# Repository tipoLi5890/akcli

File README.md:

<div align="center">

<p><strong>The verification layer that makes AI-written KiCad schematics safe to apply — a zero-dependency (pure-stdlib Python) CLI.</strong></p>

<p>

</p>

<p><strong>English</strong> · <a href=".github/README.zh-Hant.md">繁體中文</a> · <a href=".github/README.zh-Hans.md">简体中文</a> · <a href=".github/README.ja.md">日本語</a></p>

</div>

---

**akcli** is a zero-dependency Python CLI for **AI-native schematic design on KiCad** — a scriptable
design loop that you or **any AI agent** can drive end to end (bundled plugins/skills ship for Claude
Code, Codex, and OpenCode, but a shell is all it takes). Writing is the capability; verification is what makes it safe to use —
every edit is dry-run by default, net-diffed and connectivity-gated. Author a `.kicad_sch` from a JSON op-list,
run ERC / design-review / BOM / schematic ↔ PCB checks, simulate on ngspice, and source real
JLCPCB/LCSC parts. Existing Altium `.SchDoc` / `.SchLib` / `.PcbDoc` / `.PcbLib` designs import
read-only — an on-ramp into the KiCad flow, which is where all development happens.

## Install

Zero runtime dependencies; needs **Python ≥ 3.11** (for stdlib `tomllib`). The distribution is
`akcli-kicad`; the command is `akcli`:

```bash
pipx install akcli-kicad        # or: pip install akcli-kicad
akcli --version

# or run straight from a clone, no install
git clone https://github.com/tipoLi5890/akcli
./akcli/bin/akcli --help        # wrapper auto-selects a Python ≥ 3.11
```

Claude Code plugin (marketplace name `akcli`):

```text
/plugin marketplace add tipoLi5890/akcli
/plugin install akcli@akcli
```

Codex plugin (same name `akcli`):

```bash
codex plugin marketplace add tipoLi5890/akcli   # or `add ./` from a clone
codex plugin install akcli@akcli
```

Full details, per-agent setup, and troubleshooting in [INSTALL.md](INSTALL.md).

## Quickstart

Scaffold a real KiCad project with a worked example, then read, check, and draw into it — straight
from the shell:

```bash
akcli project new demo --example voltage-divider                  # .kicad_pro/.kicad_sch/.kicad_pcb/lib tables/ops.json
cd demo
akcli read  demo.kicad_sch --summary                              # normalized JSON, context-budgeted
akcli check demo.kicad_sch                                        # ERC-lite + power + BOM + connectivity + integrity
akcli draw  demo.kicad_sch --ops ops.json                         # dry-run: shows changes + net diff
akcli draw  demo.kicad_sch --ops ops.json --apply --strict-nets   # atomic write + verify + backup
akcli project check                                               # project-integrity findings (still 0)
akcli undo  demo.kicad_sch                                        # revert the last write
```

Every write is a dry run by default; `--apply` goes through an atomic snapshot → temp → verify →
replace pipeline with a pure-Python connectivity gate, and `akcli undo` reverts from a rotated backup
stack. Altium files are read-only offline.

## What it does

One normalized model behind every command, so each check, diff, and report works on a KiCad
`.kicad_sch` — and just the same on an imported Altium `.SchDoc`:

| Command | What it does |
|---|---|
| `read` · `net` · `component` · `pins` | Parse KiCad or Altium into one normalized JSON model; query nets (whole-net or pin-level: `net --at` / `--same` / `--why`), components, and pin coordinates. |
| `project` · `new` · `plan` · `draw` · `ops` · `arrange` | Scaffold a complete KiCad project (`.kicad_pro`/`.kicad_pcb`/lib tables, optionally `--example NAME`) from scratch, or adopt an existing `.kicad_sch` into one (`project new`/`project init`), inspect what it binds (`project info`) and gate its integrity (`project check`), then author it — a root file, a child sheet, or **several sheets in one atomic transaction** (the `sheets` envelope + per-op `sheet` routing, with run backups and `undo --run`) — from a versioned **22-op + 10-macro** JSON op-list, behind a net-diff safety gate evaluated over the **whole sheet tree** and one-command `undo`; `ops from-intent` compiles a design document (declared nets + components) straight into an op-list. Symbols resolve from `--symbols`, the config paths, then the project and global `sym-lib-table`. |
| `check` · `verify` · `diff` · `pinmap` | ERC-lite + power + BOM + document-integrity + intent / contract checks, schematic ↔ PCB equivalence (`verify --library` also compares each board footprint with its library source), net-membership diff, MCU pin → net map. |
| `review` | Advisory, confidence-graded design review across six detector families (signal / validation / pcb / emc / domain / gerber); DNP parts satisfy no rule. |
| `sim` | Render to a SPICE deck and assert on KiCad's bundled ngspice; sweep corners; fit diode models from datasheet points. Component values are normalized, or refused rather than guessed. |
| `jlc` | Search JLCPCB/LCSC (stock, price, Basic/Extended), convert a part into a KiCad library in-process (typed pins, real `Value`), fetch datasheets. |
| `calc` | **60** standards-cited offline calculators (E-series, IPC-2221, impedance, I²C pull-ups, buck/boost…), each citing its reference. |
| `library` · `fab` · `release` | Library-workspace audit/repair, symbol authoring from a pin table (`new-symbol` — you give the pin table, akcli computes the coordinates) with a standalone lint (`lint-symbols`) and a coincident-pin check that gates the write, versioned fab-profile checks (bundled profiles selectable by id via `fab profiles`; the real outline, vias, tenting and project design rules are read from the board), a committed library baseline (`library audit --write-baseline`), and a release preflight (including KiCad DRC) that writes a traceable manifest with tool, gerber and profile evidence. |
| `gate` | Iteration-weight bundle of the four checks re-run after every GUI edit round (the full `check` set, intent assertions, sch ↔ PCB `verify`, BOM-lock drift — offline by default) — zero-argument in a configured project; `release preflight` stays the release-weight gate. |
| `export` · `render` · `doc` · `view` | Netlist export (Protel / KiCad / CSV — the KiCad form carries the UUID sheetpath identity a re-import needs), pure-stdlib SVG render, a Markdown pinout book, and a localhost `/calc` + `/live` dashboard. |
| `capabilities` · `schema` | The self-describing surface manifest — whole, per-section (`--section`), or per-command (`--command draw`) — and every packaged JSON Schema printed byte-for-byte for client-side validation. |

Two headline examples — a design review and a part search:

```bash
akcli review analyze board.kicad_sch --profile deep --pcb board.kicad_pcb   # advisory findings + evidence
akcli jlc search "0.1uF 0402 X7R"                                           # JLCPCB/LCSC catalog (needs network)
```

## Use with AI agents

`akcli` is a plain CLI, so any shell-capable agent can drive it. Commands emit structured JSON with
`--json` (carrying a version stamp — `schema_version`, or a family field like `proposals_version` /
`facts_version`), each op-list carries a `protocol_version`, and `akcli
capabilities` self-describes the entire CLI surface in one JSON document — and every error code ships a
machine-readable `remediation` hint.

- **Claude Code** — install the bundled plugin for 8 `/akcli:circuit-*` commands (review, pinmap,
  draw, diff, parts, sim, datasheet, release) plus 13 skills spanning design, review, authoring, Altium interop, parts
  sourcing, calculators, and release gating.
- **Codex** — install the bundled plugin, or drop the loose skill folders into `.agents/skills/` for
  auto-discovery. See [docs/codex-plugin.md](docs/codex-plugin.md).
- **OpenCode** — auto-discovers the bundled skills; see
  [INSTALL.md](INSTALL.md#use-with-ai-coding-agents) for the exact commands.

## Why akcli

- **Zero runtime dependencies.** Standard library only (including `tomllib`) — easy to vendor, sandbox,
  or run in CI.
- **Purpose-built for KiCad.** An iterative KiCad S-expression parser and byte-stable writer at the
  core; Altium designs come in read-only through pure-stdlib OLE2/CFBF record decoding, straight into
  the same KiCad flow. No compiled extensions.
- **Byte-identical re-apply.** Deterministic UUIDv5 + replace-in-place makes every edit idempotent —
  re-running an op-list produces the same bytes.
- **Connectivity is the only hard write gate.** Every `plan`/`draw` prints a before/after net diff
  (splits, merges, moves, renames — matched by pin membership, never by name); `--strict-nets` refuses a
  write that splits, merges or moves a named net.
- **Net inference you can trust.** A rebuilt net layer handles global same-name merges, junctions,
  T-junctions, and No-ERC markers — fixing the classic "same-named nets split into single-pin nets" bug.

## Optional external tools

"Zero-dependency" means zero Python **package** dependencies: `pip install` pulls in nothing, and the
entire core loop (read / plan / draw / check / diff / calc / render) runs on the standard library
alone. A few features can use something outside Python — always detected at runtime, never required
by the core loop:

| Feature | Uses | If missing |
|---|---|---|
| Advisory ERC second opinion, `view live` SVG | `kicad-cli` (local executable) | Skipped silently — non-fatal, results stay advisory. |
| `sim` execution (`--deck-only` needs nothing) | libngspice (bundled with KiCad) | `sim` exits with `NGSPICE_MISSING`; everything else unaffected. |
| Standard symbol nicknames (`Device:R`, `power:*`) | `kicad-cli` install location (derives `${KICAD*_SYMBOL_DIR}`) | Symbols resolve only from explicit `--symbols` / config paths. |
| `jlc` part search / datasheet fetch | Network | The **only** networked command family; all others are fully offline. |

`akcli doctor` probes each of these and prints per-OS remediation.

## Documentation

| Doc | Covers |
|---|---|
| [SPEC.md](docs/SPEC.md) | Data model, config tables, JSON schemas |
| [cli-reference.md](docs/cli-reference.md) | Every command and flag |
| [op-list-authoring.md](docs/op-list-authoring.md) | Op-list authoring bible (ops, macros, groups) |
| [design-integrity.md](docs/design-integrity.md) | Contracts, fab profiles, release preflight |
| [review-rules.md](docs/review-rules.md) | Design-review rule catalogue |
| [sim.md](docs/sim.md) | Simulation reference |
| [agent-state.md](docs/agent-state.md) | Workspace state files and the multi-agent contract |
| [codex-plugin.md](docs/codex-plugin.md) | Codex plugin layout and bundled skills |
| [jlc.md](docs/jlc.md) | `akcli jlc`: part search, BOM purchasability, datasheet fetch, JLCPCB manufacturing handoff |
| [kicad-format-gotchas.md](docs/kicad-format-gotchas.md) | KiCad file-format rules for safe editing |
| [pin-identity.md](docs/pin-identity.md) | Pin identity model audit ahead of v1.0 |
| [migration-0.21.md](docs/migration-0.21.md) | Migrating to the 0.21 contract (`protocol_version` 2, schema 2.0) |
| [releasing.md](docs/releasing.md) | Release runbook |
| [recipes/](docs/recipes/README.md) | CI workflow recipes (gating schematic pull requests) |
| [stability.md](docs/stability.md) | Public contract surfaces, what is not contract, versioning rules |
| [ROADMAP.md](ROADMAP.md) | Roadmap to v1.0 with exit criteria |

## Roadmap

**Shipped (v0.24.0):** release gates for KiCad DRC, a committed library baseline, a PCB ↔ library
check and tree-scoped integrity, with `fab check` reading the board's real outline, vias, tenting and
project design rules; before that, complete KiCad project scaffolding — `project new` / `project init` write the
`.kicad_pro`, a blank `.kicad_pcb` board container, the project lib tables and a `.gitignore` around a
root sheet (`--example NAME` drops in a worked op-list), while `project info` / `project check` read
and gate what the project binds — KiCad write/draw from a 22-op + 10-macro vocabulary (hierarchical
`add_sheet`, optionally creating the child sheet inside the same transaction with `"create": true`,
writes into a child sheet of an existing hierarchy and across several sheets in one atomic
transaction, a net-diff safety rail evaluated over the whole sheet tree, per-instance references on
a reused sheet, `new` / multi-level `undo` / `undo --run`), net-preserving `arrange --groups` re-layout, the advisory `akcli review` engine (six
detector families, now including power-entry protection, plus a datasheet facts store, `propose` /
`tree` / `validate`), ERC / power / BOM / diff / pinmap / intent / contract checks with waivers
(SARIF from `check --format sarif` / `review report --format sarif`), read-only document `check --integrity`, schematic ↔ PCB `verify`, a project `library`
workspace, versioned `fab` profiles, a `release preflight` gate, `akcli sim` on KiCad's bundled
ngspice, JLCPCB/LCSC sourcing with datasheet fetch, 60 standards-cited calculators, pure-stdlib SVG
rendering that draws the real symbol artwork from KiCad `lib_symbols`, and version-tolerant
Altium/KiCad readers. Standard symbol nicknames resolve on a stock KiCad install: the compiled-in
`${KICAD*_SYMBOL_DIR}` paths are derived from the located `kicad-cli`, and `akcli doctor` reports
whether that resolution works here.

**Ahead (→ v1.0):** the contract-freeze audit. The first PyPI release (`pip install akcli-kicad`) shipped in 0.15.0.
A workflow recipe that gates schematic PRs ships in [docs/recipes/](docs/recipes/README.md). *Deferred
by decision:* a packaged Marketplace Action, the `view` waveform panel, and a native MCP server (the
plain CLI serves agents today). Full plan with exit criteria in
[ROADMAP.md](ROADMAP.md).

## Acknowledgments

`akcli jlc` builds on (full attribution in [ACKNOWLEDGMENTS.md](ACKNOWLEDGMENTS.md) and
[THIRD_PARTY_NOTICES.md](THIRD_PARTY_NOTICES.md)):

- **JLC2KiCadLib** by **TousstNicolas** (MIT) — LCSC → KiCad conversion core, vendored.
- **jlcsearch** (tscircuit, MIT) and **jlcparts** (MIT) — part-search backend.
- **EasyEDA / LCSC / JLCPCB** — component data source.

## Contact

Questions, bugs, or feature requests: please
[open a GitHub issue](https://github.com/tipoLi5890/akcli/issues).

## License

MIT © 2026 Li, ching yu. See [LICENSE](LICENSE); third-party attribution in
[ACKNOWLEDGMENTS.md](ACKNOWLEDGMENTS.md) and [THIRD_PARTY_NOTICES.md](THIRD_PARTY_NOTICES.md), and the
security model in [SECURITY.md](SECURITY.md).

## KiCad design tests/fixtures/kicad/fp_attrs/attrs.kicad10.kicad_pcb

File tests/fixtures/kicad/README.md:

# Synthetic KiCad fixtures

Hand-authored, valid S-expression KiCad files used by the KiCad reader/netbuild tests.
The dev/CI box has **no KiCad libraries installed**, so every symbol these schematics
reference is vendored here and also cached inline (`lib_symbols`) in each schematic.
Every **schematic** here is hand-authored — coordinates and UUIDs are hand-chosen so the
files are small and reviewable. The exceptions are the three `netlist_*.kicad10.net` files,
which *are* real `kicad-cli` exports kept as netlist ground truth (see below).

## Netlist ground truth

`netlist_power_entry.kicad10.net` — `kicad-cli 10.0.4 sch export netlist` run on
`tests/fixtures/corpus/power_entry.kicad_sch`. It pins the grammar and the UUID identity
(`(design)`, per-comp `(sheetpath)` + `(tstamps)`, `(libparts)`) that
`src/akcli/exporters.py` must agree with, so `tests/test_e2e_netlist.py` can arbitrate the
exporter **everywhere**, not only on a box with KiCad installed (where the same test
re-derives it live and asserts the fixture has not rotted).

`netlist_hier_root.kicad10.net` — the same, run on `hier/root.kicad_sch` (below). It pins
**net NAMING** across a hierarchy, the rule a flat board cannot show.

Four machine-specific atoms were normalized on commit; nothing structural was touched:

| Field | KiCad wrote | Committed as |
|---|---|---|
| `(design (source ..))` | absolute path of the dev checkout | repo-relative posix path |
| `(design (date ..))` | export wall-clock time | `""` (determinism) |
| `(comp (property (name "Sheetname") (value ..)))` | localized root-sheet name | `"Root"` |
| `(libraries (library (uri ..)))` | `${KICAD10_SYMBOL_DIR}` | `${KICAD_SYMBOL_DIR}` |

## `hier/` — hierarchical net-name ground truth

`hier/root.kicad_sch` instantiates `hier/amp.kicad_sch` **twice** (`Amp`, `Amp Two`), and
that child instantiates `hier/deep.kicad_sch` once (`Deep`) — five sheet instances in all.
It exists to pin one rule: eeschema qualifies a net name with the **human-readable sheet
path** of its driver, unless the driver is a global label or a power pin.

| driver | net name KiCad writes |
|---|---|
| `(label "ROOT_LOCAL")` on the root sheet | `/ROOT_LOCAL` |
| `(label "AMP_LOCAL")` on a child sheet | `/Amp/AMP_LOCAL`, `/Amp Two/AMP_LOCAL` |
| `(label "DEEP_LOCAL")` on a grandchild sheet | `/Amp/Deep/DEEP_LOCAL` |
| `(hierarchical_label "DEEP_OUT")`, parent pin unlabelled | `/Amp/Deep/DEEP_OUT` |
| `(global_label "AMP_GLOBAL")` | `AMP_GLOBAL` — never qualified |
| `power:GND` symbol | `GND` — never qualified |

Every net here carries exactly **one** name, so the fixture tests the qualification rule
without depending on how ties between several names on one net are broken (akcli's pick is
priority-then-alphabetical; eeschema's is GLOBAL > POWER_PIN > LOCAL_LABEL > HIER_LABEL —
they historically disagreed on the `MID`/`VOUT` node of `board_v8` below;
since 0.21 both name it `VOUT`).

The child sheets live in a subdirectory on purpose: `tests/test_roundtrip_netlist.py` globs
`tests/fixtures/kicad/*.kicad_sch` and copies each file **alone** into a temp dir, which a
multi-file design cannot survive.

## `hier_partial/` — reference-resolution ground truth

`root.kicad_sch` instantiates `amp.kicad_sch` twice (`Amp`, `Amp Two`). One resistor
(`…00000000000b`) carries only the first instance's entry (`R102`); its `Reference`
property is `R?`. KiCad writes `R102` on BOTH sheet instances — the symbol's first
entry, never the property — and reports annotation errors
(`netlist_hier_partial_root.kicad10.net`, kicad-cli 10.0.4). akcli resolves the same way
(`readers/kicad.py::_reference`), and `check --integrity` reports the duplicate (the one
`_TREE_ALLOWLIST` entry in `tests/test_check_integrity.py`). Each file alone is clean.

## Versions covered

| File | KiCad version | `(version ...)` | Format markers |
|---|---|---|---|
| `board_v7.kicad_sch` | KiCad 7.0 | `20230121` | bare `hide`, `(pin_numbers hide)`, `(fields_autoplaced)`, no `generator_version`, no `exclude_from_sim` |
| `board_v8.kicad_sch` | KiCad 8.0 | `20231120` | `(hide yes)`, `(pin_numbers (hide yes))`, `(fields_autoplaced yes)`, `(generator_version "8.0")`, `(exclude_from_sim no)` |
| `symbols/Device.kicad_sym` | KiCad 8.0 | `20231120` | `R`, `C`, `L`, and `C_Polarized` (`(extends "C")`) |
| `symbols/power.kicad_sym` | KiCad 8.0 | `20231120` | `GND`, `+3V3` power symbols |

The v7/v8 schematics are otherwise **identical circuits** — same components, coordinates
and topology — so a reader test can assert the two format versions parse to the same model.

## Symbol libraries

* `symbols/Device.kicad_sym` — `R`, `C`, `L` (each a passive 2-pin part with pins carrying
  electrical types) plus `C_Polarized`, which uses `(extends "C")` and therefore inherits
  its pins from `C` (exercises the `kicad_lib` extends-resolution path).
* `symbols/power.kicad_sym` — `GND` and `+3V3` power symbols, each a single `power_in` pin
  at the symbol origin `(at 0 0 ...)`.

Pin connection points (the `(at ...)` of each `pin`) are in symbol-local coordinates with
KiCad's library convention (+Y up). A placed instance at `(at PX PY 0)` (rotation 0, no
mirror) puts pin number `N` at world `(PX + lx, PY - ly)`.

## Circuit in board_v7 / board_v8

A resistor divider with a decoupling cap — small but enough for net inference:

```
        +3V3 (#PWR01)
          |
         R1  10k   (Device:R @ 50.8,50.8)
          |
    MID──+────VOUT──── C1.1            <- net "VOUT" (global wins), local label "MID"
          |            |
         R2  10k      C1  100n          (R2 @ 50.8,63.5 ; C1 @ 66.04,63.5)
          |            |
          +─────+──────+                <- net "GND"
                |
               GND (#PWR02)
```

Expected nets (component-pin membership):

| net | source | members |
|---|---|---|
| `+3V3` | power port `#PWR01` | `R1.1` |
| `VOUT` (aka `MID`) | local `label` + `global_label` | `R1.2`, `R2.1`, `C1.1` |
| `GND` | power port `#PWR02` | `R2.2`, `C1.2` |

Each file contains: an inline `(lib_symbols ...)` cache, 5 symbol instances (R1, R2, C1
plus the two `#PWR` power symbols) each with a `(lib_id ...)` and a synced
`(instances ... (path ... (reference ...)))`, five `(wire ...)` segments, two
`(junction ...)` dots, one `(label ...)`, one `(global_label ...)`, and the GND/+3V3
power symbols. The `VOUT` net carries both a local label (`MID`) and a global label
(`VOUT`) on the same node, so it doubles as a multi-name / alias case for netbuild.

`tests/test_kicad_fixtures.py` validates these files structurally (balanced
S-expressions, required elements present, the v7/v8 format-marker differences) and
re-derives the three nets with a self-contained mini-parser to prove the hand-placed
wire endpoints actually coincide with the computed pin world-coordinates.

## `blank_project/` — project-scaffold ground truth

`blank.kicad_pro`, `blank.kicad_pcb`, `sym-lib-table`, `fp-lib-table` are the exact
bytes `akcli project new` writes for the non-schematic half of a KiCad project. Unlike
the schematics above these are **not hand-authored**: the project file is KiCad's own
`share/kicad/template/kicad.kicad_pro` with `meta.filename` + `sheets` filled in, and
the board's header/layers block is transcribed verbatim from
`share/kicad/template/Arduino_Mega/Arduino_Mega.kicad_pcb` (file version `20241229`,
new-style layer numbering). Nothing here is invented; see the module docstring of
`src/akcli/writers/blank.py` for why.

The `.kicad_pro` fixture pins the UUID `00000000-0000-4000-8000-000000000001` so the
file is byte-stable — `tests/test_scaffold.py` substitutes it when comparing against the
emitter, and asserts byte equality in both directions.

The board is a **container, not a layout**: zero footprints, zero tracks, no outline.
`tests/test_e2e_project.py` runs a real `kicad-cli pcb drc` / `pcb export svg` over both
the fixture and a freshly scaffolded project and requires exit 0; the single expected
`invalid_outline` violation is the "there is no outline" fact, not a defect.

Regenerate (only when the emitter deliberately changes, and re-run the e2e file):

```
PYTHONPATH=src python3 -c "
from pathlib import Path
from akcli.writers import blank
d = Path('tests/fixtures/kicad/blank_project')
u = '00000000-0000-4000-8000-000000000001'
d.joinpath('blank.kicad_pro').write_text(blank.blank_pro('blank.kicad_pro', u), encoding='utf-8', newline='\n')
d.joinpath('blank.kicad_pcb').write_text(blank.blank_pcb('A4'), encoding='utf-8', newline='\n')
d.joinpath('sym-lib-table').write_text(blank.blank_lib_table('sym'), encoding='utf-8', newline='\n')
d.joinpath('fp-lib-table').write_text(blank.blank_lib_table('fp'), encoding='utf-8', newline='\n')
"
```

## `drc_demo/` — KiCad DRC report ground truth

`release preflight --drc` turns `kicad-cli pcb drc --format json` output into gate
findings. The report shape is therefore a KiCad grammar claim, and this directory is its
ground truth: a board, its project file, and the **real** reports kicad-cli wrote for it.

| File | What it is |
|---|---|
| `drc_demo.kicad_pcb` | hand-authored, minimal: the `blank_project` header/layers, an `Edge.Cuts` rectangle, `R1` + `C1` (every footprint, pad and track carries a hand-chosen uuid), and four `F.Cu` segments |
| `drc_demo.kicad_pro` | `blank_project/blank.kicad_pro` with `meta.filename` set, `sheets` emptied, and `board.design_settings.rule_severities` turning `lib_footprint_issues` + `lib_footprint_mismatch` to `ignore` |
| `drc_demo.drc.kicad10.json` | `kicad-cli 10.0.4 pcb drc --format json --severity-error --severity-warning`, KiCad UI language English |
| `drc_demo.drc.kicad10.zh_TW.json` | the same run with KiCad's UI language at its macOS-system default (zh_TW) |

The board is built to produce exactly three entries, one of each kind the gate maps:

| KiCad `type` | severity | cause | items (uuid suffix) |
|---|---|---|---|
| `clearance` | error | the `SIG` segment runs 0.05 mm beside the `GND` segment (default clearance 0.2 mm) | tracks `…402`, `…404` |
| `track_dangling` | warning | the `SIG` segment connects to nothing | track `…404` |
| `unconnected_items` | error | `+3V3` is never routed | pads `…111` (R1.1), `…211` (C1.1) |

Three properties of kicad-cli that the fixture pins, and that
`src/akcli/drivers/kicad_cli.py` is written around:

* **Descriptions are localized.** The two reports differ in every `description`
  (`Pad 1 [+3V3] of R1 on F.Cu` vs `1 上 [+3V3] 的焊盤 R1 F.Cu`) and in nothing else — so
  the gate keys on `type` / `severity` / `uuid` / `pos` and resolves designators and nets
  by looking the item `uuid` up in the board file, never by parsing text.
* **An item with no uuid in the file gets a fresh one at every load** (the pads of
  `../board.kicad_pcb` do): such an item resolves to nothing, which is why every item
  here carries one.
* **`pcb drc` writes into the project directory**: it creates `<board>.kicad_prl` beside
  the board when none exists — even when the board fails to load. The driver therefore
  runs KiCad on a staged copy; `tests/test_kicad_cli.py` asserts this directory is
  byte-identical before and after a real run. The `rule_severities` in the project file
  double as the proof that the `.kicad_pro` travels into that copy: without it KiCad
  falls back to defaults and reports `lib_footprint_*` for both footprints (which, being
  a function of the footprint libraries installed on the machine, would also make the
  report non-reproducible).

One atom was normalized on commit: `"date"` (run wall-clock time) → `""`. `kicad_version`
is kept as written. `tests/test_kicad_cli.py` re-runs kicad-cli on the board wherever it
is installed and compares every locale- and clock-independent field against the English
report.

Regenerate (only when the board deliberately changes; a throwaway `KICAD_CONFIG_HOME`
keeps the language choice out of your own KiCad settings, and the run happens on a copy
so no `.kicad_prl` lands here):

```
tmp=$(mktemp -d); mkdir -p "$tmp/proj" "$tmp/cfg/10.0"
cp tests/fixtures/kicad/drc_demo/drc_demo.kicad_p* "$tmp/proj/"
printf '{"system": {"language": "English"}}\n' > "$tmp/cfg/10.0/kicad_common.json"
KICAD_CONFIG_HOME="$tmp/cfg" kicad-cli pcb drc --format json --severity-error \
  --severity-warning --output "$tmp/drc.json" "$tmp/proj/drc_demo.kicad_pcb"
# then blank the "date" value and copy $tmp/drc.json over drc_demo.drc.kicad10.json
```

## `altium_import/` — KiCad's Altium footprint importer, frozen

`AKCLI_GFX.kicad_mod`, `AKCLI_LAYERS.kicad_mod` and `AKCLI_SKIP.kicad_mod` are what
`kicad-cli 10.0.4 fp upgrade` wrote when it converted a **synthetic** Altium `.PcbLib` —
the one `tests/test_pcblib_graphics.py::_oracle_library` builds from hand-packed records,
so no real library is involved. They are committed byte-for-byte as KiCad wrote them
(nothing normalized: the files hold no path, date or user name) and are ground truth for
`akcli library import-altium`:

| File | Pins |
|---|---|
| `AKCLI_GFX` | pads, tracks → `fp_line`, arcs → `fp_arc` (which end KiCad starts from, and which side `mid` falls on), a 0°–360° arc → `fp_circle`, a full turn written with other angles → a closed `fp_arc` |
| `AKCLI_LAYERS` | one track per Altium layer id akcli maps: the KiCad layer each lands on |
| `AKCLI_SKIP` | what akcli does **not** copy from KiCad's importer: keepout objects (rule areas), a `MultiLayer` track (one copy on each of 32 copper layers), an internal-plane track (a rule area on layer `UNDEFINED`), a mechanical layer past 45 (dropped) |

`tests/test_pcblib_graphics.py` compares akcli's import of the same synthetic library
against these files on every platform, and — wherever `kicad-cli` is installed — re-runs
the conversion and asserts the files have not rotted.

Regenerate (only when `_oracle_library` deliberately changes):

```
PYTHONPATH=src python - <<'PY'
from pathlib import Path
from tests import test_pcblib_graphics as G
G._oracle_library(Path("/tmp/akcli_oracle.PcbLib"))
PY
kicad-cli fp upgrade --force --output /tmp/akcli_oracle.pretty /tmp/akcli_oracle.PcbLib
cp /tmp/akcli_oracle.pretty/AKCLI_*.kicad_mod tests/fixtures/kicad/altium_import/
```

## `fp_attrs/` — board-footprint attribute ground truth

`readers/kicad.py::read_pcb` takes a footprint's placement, assembly flags and 3D models
from its `(at …)`, `(attr …)` and `(model …)` nodes, and `verify` acts on them (DNP / BOM
mismatches, the `board_only` demotion, `verify --library`). What those nodes look like is a
KiCad grammar claim, so this directory holds what a real KiCad wrote.

| File | What it is |
|---|---|
| `attrs_v8.kicad_pcb` | hand-authored input, KiCad 8 syntax (`20240108`): six footprints covering every attribute form below |
| `attrs.kicad10.kicad_pcb` | **`kicad-cli 10.0.4 pcb upgrade`** of that input (`20260206`), then one `(variant …)` block inserted by hand into `R1` and the file re-saved with `pcb upgrade --force` — so KiCad parsed and re-wrote the block |
| `legacy_v5.kicad_pcb` | hand-authored input, KiCad 5 syntax (`20171130`, `(module …)` nodes) |
| `legacy_v5.kicad10.kicad_pcb` | **`kicad-cli 10.0.4 pcb upgrade`** of that input |
| `proj.pretty/*.kicad_mod` | **`kicad-cli 10.0.4 fp upgrade`** output of four hand-authored footprints — the library the board's `proj:` footprints come from |
| `fp-lib-table` | hand-authored: `proj` → `${KIPRJMOD}/proj.pretty` |
| `3d/*.step` | placeholders (not STEP bodies): only their existence and bytes matter |

What KiCad 10 wrote, per input form:

| Input (`attrs_v8` / `legacy_v5`) | KiCad 10 output | Reader |
|---|---|---|
| `(attr smd)` | unchanged | no flag — a type token (`smd` / `through_hole`) is not a flag |
| `(attr smd exclude_from_pos_files exclude_from_bom dnp)` | unchanged | `dnp`, `exclude_from_bom`, `exclude_from_pos` |
| `(attr board_only exclude_from_pos_files exclude_from_bom allow_missing_courtyard allow_soldermask_bridges)` | same tokens, **wrapped over three lines**; no type token (footprint type "unspecified") | `board_only`, `exclude_from_bom`, `exclude_from_pos` |
| no `(attr …)` node at all (`TP1`) | still none | no flag |
| v5 `(module … (attr virtual))` | `(attr exclude_from_pos_files exclude_from_bom)` | both exclusions, **not** `board_only` |
| v5 `(module …)` with a through-hole pad and no `attr` | `(attr through_hole)` | no flag |
| `(at 110 100 270)` (v5) | `(at 110 100 -90)` | `rotation` kept as written (`-90.0`) |
| `(model "…" (hide yes) …)` | unchanged | still a model reference |

Four properties the reader is built on:

* **DNP is a token of `(attr …)`, in every version through KiCad 10.** There is no
  footprint-level `(dnp yes)` node on a board (that spelling belongs to the *schematic*):
  kicad-cli 10.0.4 refuses to load a board whose footprint carries one —
  `test_e2e_footprint_level_dnp_node_is_not_kicad_grammar` re-proves it live.
* **KiCad 10 adds per-footprint `(variant (name "NoFit") (dnp yes) (exclude_from_bom yes)
  (exclude_from_pos_files yes))` blocks** (also `(field (name …) (value …))`; `(in_bom …)` is
  refused there). They are assembly-variant overrides, not the footprint's own flags: `R1`
  carries one while its `(attr smd)` says fitted, and the reader reports the base flags. Only
  the footprint's **own** children are read (`SNode.find_all` is not recursive), which is what
  keeps the nested `(dnp yes)` out.
* **`virtual` means "not in BOM, not in position files"** — KiCad rewrites it to exactly those
  two tokens, for a v5 `(module …)` and for a `(footprint … (attr virtual))` alike.
* **KiCad re-orders footprints on save** (the `B.Cu` footprint `J1` moves last), so tests key on
  the designator, never on position in the file.

`read_pcb` reads `(footprint …)` nodes only: the un-upgraded `legacy_v5.kicad_pcb` yields no
footprints at all (pre-existing behaviour, unrelated to attributes). It is committed as the
*input* of the upgrade, not as a reader case.

Real KiCad 9 output (`20241229`) was checked against the template boards KiCad ships
(`share/kicad/template/*/*.kicad_pcb`: `(attr board_only exclude_from_pos_files
exclude_from_bom)`, `(attr exclude_from_pos_files)`, `(attr through_hole)` — the same grammar).
They are not committed; `test_e2e_boards_shipped_with_kicad_read_consistently` re-reads whatever
templates sit beside the installed kicad-cli.

`tests/test_fp_attrs.py` pins all of the above, and — where kicad-cli is installed — re-runs
both upgrades and compares the PARSED fields with the committed output (not bytes: KiCad mints
fresh uuids for the `Datasheet` / `Description` properties it adds on every save).
`tests/test_fplib.py` and `tests/test_library_baseline.py` use the directory as a project.

Regenerate (only when an input deliberately changes; a throwaway `KICAD_CONFIG_HOME` keeps the
run out of your own KiCad settings, and it happens on copies because `pcb upgrade` rewrites its
argument in place and drops a `.kicad_prl` beside it):

```
tmp=$(mktemp -d); mkdir -p "$tmp/cfg/10.0"; d=tests/fixtures/kicad/fp_attrs
printf '{"system": {"language": "English"}}\n' > "$tmp/cfg/10.0/kicad_common.json"
export KICAD_CONFIG_HOME="$tmp/cfg"
cp $d/attrs_v8.kicad_pcb "$tmp/attrs.kicad_pcb";   kicad-cli pcb upgrade "$tmp/attrs.kicad_pcb"
cp $d/legacy_v5.kicad_pcb "$tmp/legacy.kicad_pcb"; kicad-cli pcb upgrade "$tmp/legacy.kicad_pcb"
# insert after R1's "(attr smd)" in $tmp/attrs.kicad_pcb:
#   (variant (name "NoFit") (dnp yes) (exclude_from_bom yes) (exclude_from_pos_files yes))
kicad-cli pcb upgrade --force "$tmp/attrs.kicad_pcb"
# then copy $tmp/attrs.kicad_pcb -> attrs.kicad10.kicad_pcb, $tmp/legacy.kicad_pcb -> legacy_v5.kicad10.kicad_pcb
```

## `fab/` — outline, via, tenting and drill ground truth for `akcli fab check`

What `read_pcb` tells `fab check` about a board — its true `Edge.Cuts` area, each via's type
and tenting, both dimensions of an oval drill — is a pile of KiCad grammar claims. Every board
here was **written by kicad-cli 10.0.4** (`pcb upgrade --force` of a minimal hand-authored
input, every item carrying a hand-chosen uuid; file version `20260206`), and beside each sits
what the same KiCad **measured** for it: `<name>.stats.kicad10.json` is `kicad-cli pcb export
stats --format json`, UI language English (the report localizes its `vias` / `pads` keys and
the drill `shape` / `source` values). One atom was normalized on commit: `metadata.date` → `""`.

| File | What it pins |
|---|---|
| `outline_cutouts.kicad_pcb` | a 40 × 30 mm board with r = 2 mm corners from `gr_line` + `gr_arc (start) (mid) (end)`; cutouts from `gr_circle (center) (end)`, `gr_rect`, `gr_poly` |
| `outline_circle.kicad_pcb` | a board that is ONE `gr_circle` (r = 15 mm) |
| `outline_poly_arc.kicad_pcb` | a `gr_poly` whose `pts` hold an `(arc (start) (mid) (end))` between `xy` points; the polygon closes implicitly |
| `outline_rect_radius.kicad_pcb` | KiCad 10 rounded rectangles: `(gr_rect (start) (end) (radius 2))` as the body, more as cutouts — one whose radius kicad-cli clamped (written `5`, re-saved `2`: half the short side), an `fp_rect` with `(radius 1)`, and the same in a footprint rotated 30°, which kicad-cli re-saved as an `fp_poly` of four `(arc …)` and no `xy` |
| `outline_open.kicad_pcb` | the rounded board with one corner arc missing — KiCad: `has_outline: false`, `area: null` |
| `outline_footprint.kicad_pcb` | outline pieces drawn INSIDE footprints: a back-side footprint rotated 90° supplies a notch (`fp_line` + `fp_arc`), others supply cutouts (`fp_circle`, `fp_rect`, `fp_poly`) |
| `vias_tenting.kicad_pcb` | 4 copper layers; `(setup (tenting (front yes) (back no)))`; vias: through ×3 (one following the board, one `(tenting (front no) (back no))`, one `(front yes) (back yes)`), `blind`, `buried`, a `blind` token on `In1.Cu`–`In2.Cu`, `micro`, a `blind` from the back |
| `slots.kicad_pcb` | pad drills: `(drill oval 0.8 2.2)`, `(drill oval 0.9)`, `(drill oval 2.2 0.8 (offset 0.2 0))`, `(drill 0.8)`, plated and `np_thru_hole` |
| `rules/rules_demo.kicad_pro` | a project file whose `board.design_settings.rules` object is transcribed verbatim from `share/kicad/template/Arduino_Mega/Arduino_Mega.kicad_pro` (written by KiCad 9), on the `blank_project` skeleton — in its own directory so no board here picks it up by accident |

What the real files establish (each is asserted by `tests/test_kicad_pcb_fab_facts.py`):

* **Area.** KiCad's `area` is the board bodies only; `--subtract-holes-from-board`
  (`*.stats-subtract-holes.kicad10.json`) also subtracts the `Edge.Cuts` cutouts and every
  drilled hole. KiCad tessellates arcs (5 µm error), so its numbers sit a hair under the exact
  ones: a rounded 40 × 30 board is `1196.557 mm²` to KiCad and `1196.566` analytically.
* **Chaining tolerance.** KiCad joins two outline ends 0.009 mm apart and refuses 0.011 mm —
  hence `geometry.outline.CHAIN_TOLERANCE_MM = 0.01`.
* **Footprint edges count.** Remove the footprints from `outline_footprint` and the outline no
  longer closes; a single dangling `fp_line` on `Edge.Cuts` turns `has_outline` false. (187 of
  the 15 435 footprints KiCad 10.0.4 ships draw on `Edge.Cuts`.) A back-side footprint needs no
  extra mirror, and kicad-cli re-saves an `fp_rect` in a rotated footprint as an `fp_poly`.
* **Buried vias.** KiCad 10 has a `buried` token of its own. It does **not** apply it on
  re-save: the `(via blind … "In1.Cu" "In2.Cu")` here stayed `blind`, and KiCad's statistics
  count it as blind (`through 3, blind 3, buried 1, micro 1`). akcli reports it as buried — a
  via touching neither outer layer is one — so its count is `blind 2, buried 2`.
* **Tenting.** KiCad 10 always writes the board setting, and writes a via's `(tenting …)` only
  when the via overrides it (per side: `yes` / `no` / `none`).
* **Drills.** An oval whose two sizes are equal is written with ONE number; KiCad's drill table
  still lists it as a `Slot`.
* **Not modelled: Bezier.** KiCad accepts `(gr_curve (pts (xy) (xy) (xy) (xy)))` in an outline
  (and measures it); akcli does not model it — such an outline is reported as not closed and
  the area falls back to the bounding box, with the reason. No fixture: it is a stated gap.

### Legacy grammars — hand-authored, proven by their re-save

No KiCad 5, 8 or 9 binary was available, so these three shapes could not be verified against a
file *written* by the version that used them. Each is a hand-authored input in the old grammar
plus `<name>.kicad10.kicad_pcb`, the file kicad-cli 10.0.4 made of it — the proof is that akcli
reads the input the way KiCad does.

| File | Old shape | What kicad-cli 10 made of it |
|---|---|---|
| `legacy_v5.kicad_pcb` (`20171130`) | `(gr_arc (start <centre>) (end <first point>) (angle <deg>))`, also as `fp_arc` inside a `(module …)` | `(start) (mid) (end)`; a positive angle is clockwise on screen. Same area either way: `1122.009 mm²` |
| `legacy_v5.kicad_pcb` | `(pcbplotparams (viasonmask true))` — KiCad ≤ 8 kept "do not tent vias" as a plot option | `(setup (tenting (front no) (back no)))` (`viasonmask false`, or absent → `yes` / `yes`) |
| `tenting_v9.kicad_pcb` (`20241229`) | board `(tenting front)`; vias `(tenting front back)`, `(tenting none)`, `(tenting back)` | board: front yes / back no. Vias: a NAMED side → `yes`; an unnamed one is dropped (`(tenting none)` vanishes, `(tenting back)` becomes `(front none) (back yes)`) |

The last row is the one open question. kicad-cli 10 reads an unnamed side of a KiCad 9 *via* as
"follow the board"; the token list itself reads as "not tented". Which KiCad 9 meant is
unverified, so the reader reports such a side as unknown unless the board side is itself open
(both readings then agree).

Real KiCad 9 output was checked against the template boards KiCad ships (`20241229`:
`gr_arc (start) (mid) (end)`, `gr_circle (center) (end)`, `gr_rect`, `gr_poly`, and
`(setup (tenting front back))` in all 19) — not committed; `tests/test_e2e_fab.py` measures
whatever templates sit beside the installed kicad-cli with both akcli and KiCad.

`tests/test_e2e_fab.py` re-derives everything above live wherever kicad-cli ≥ 10 is installed:
the committed statistics against a fresh export, the reader against the live numbers, and each
legacy input against a fresh re-save (parsed fields, not bytes — KiCad mints new uuids for the
properties it adds).

Regenerate (only when a board deliberately changes; on copies, because `pcb upgrade` rewrites
its argument in place and every kicad-cli run drops a `.kicad_prl` beside the board):

```
tmp=$(mktemp -d); mkdir -p "$tmp/cfg/10.0"; d=tests/fixtures/kicad/fab
printf '{"system": {"language": "English"}}\n' > "$tmp/cfg/10.0/kicad_common.json"
export KICAD_CONFIG_HOME="$tmp/cfg"
for n in outline_cutouts outline_circle outline_poly_arc outline_rect_radius outline_open outline_footprint vias_tenting slots; do
  cp "$d/$n.kicad_pcb" "$tmp/$n.kicad_pcb"; kicad-cli pcb upgrade --force "$tmp/$n.kicad_pcb"
  kicad-cli pcb export stats --format json --output "$tmp/$n.stats.kicad10.json" "$tmp/$n.kicad_pcb"
done
for n in outline_cutouts outline_rect_radius outline_footprint; do
  kicad-cli pcb export stats --format json --subtract-holes-from-board \
    --output "$tmp/$n.stats-subtract-holes.kicad10.json" "$tmp/$n.kicad_pcb"
done
for n in legacy_v5 tenting_v9; do
  cp "$d/$n.kicad_pcb" "$tmp/$n.kicad10.kicad_pcb"; kicad-cli pcb upgrade --force "$tmp/$n.kicad10.kicad_pcb"
done
# then blank "date" in each stats JSON and copy the boards + JSON back over $d
```

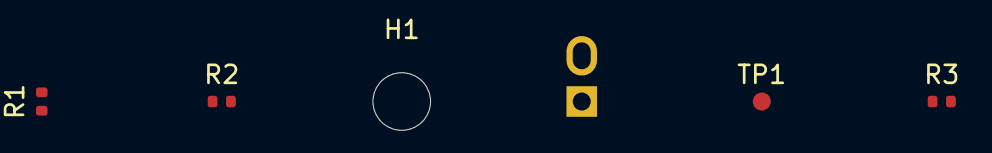
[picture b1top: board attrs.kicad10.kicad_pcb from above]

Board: 2 copper layers, 6 parts (1 on the bottom side), 3 nets, no tracks yet.

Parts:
H1: MountingHole; MountingHole_3.2mm
J1: Conn; PinHeader_1x02
R1, R2: 10k; R_0402
R3: 1k; R_0402_1005Metric
TP1: TP; TestPoint

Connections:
+3V3: J1.1, R1.1
GND: J1.2, R2.2, R3.2
SIG: R1.2, R2.1, R3.1, TP1.1
